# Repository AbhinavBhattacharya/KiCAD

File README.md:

# KiCAD
A repository of all my KiCAD projects

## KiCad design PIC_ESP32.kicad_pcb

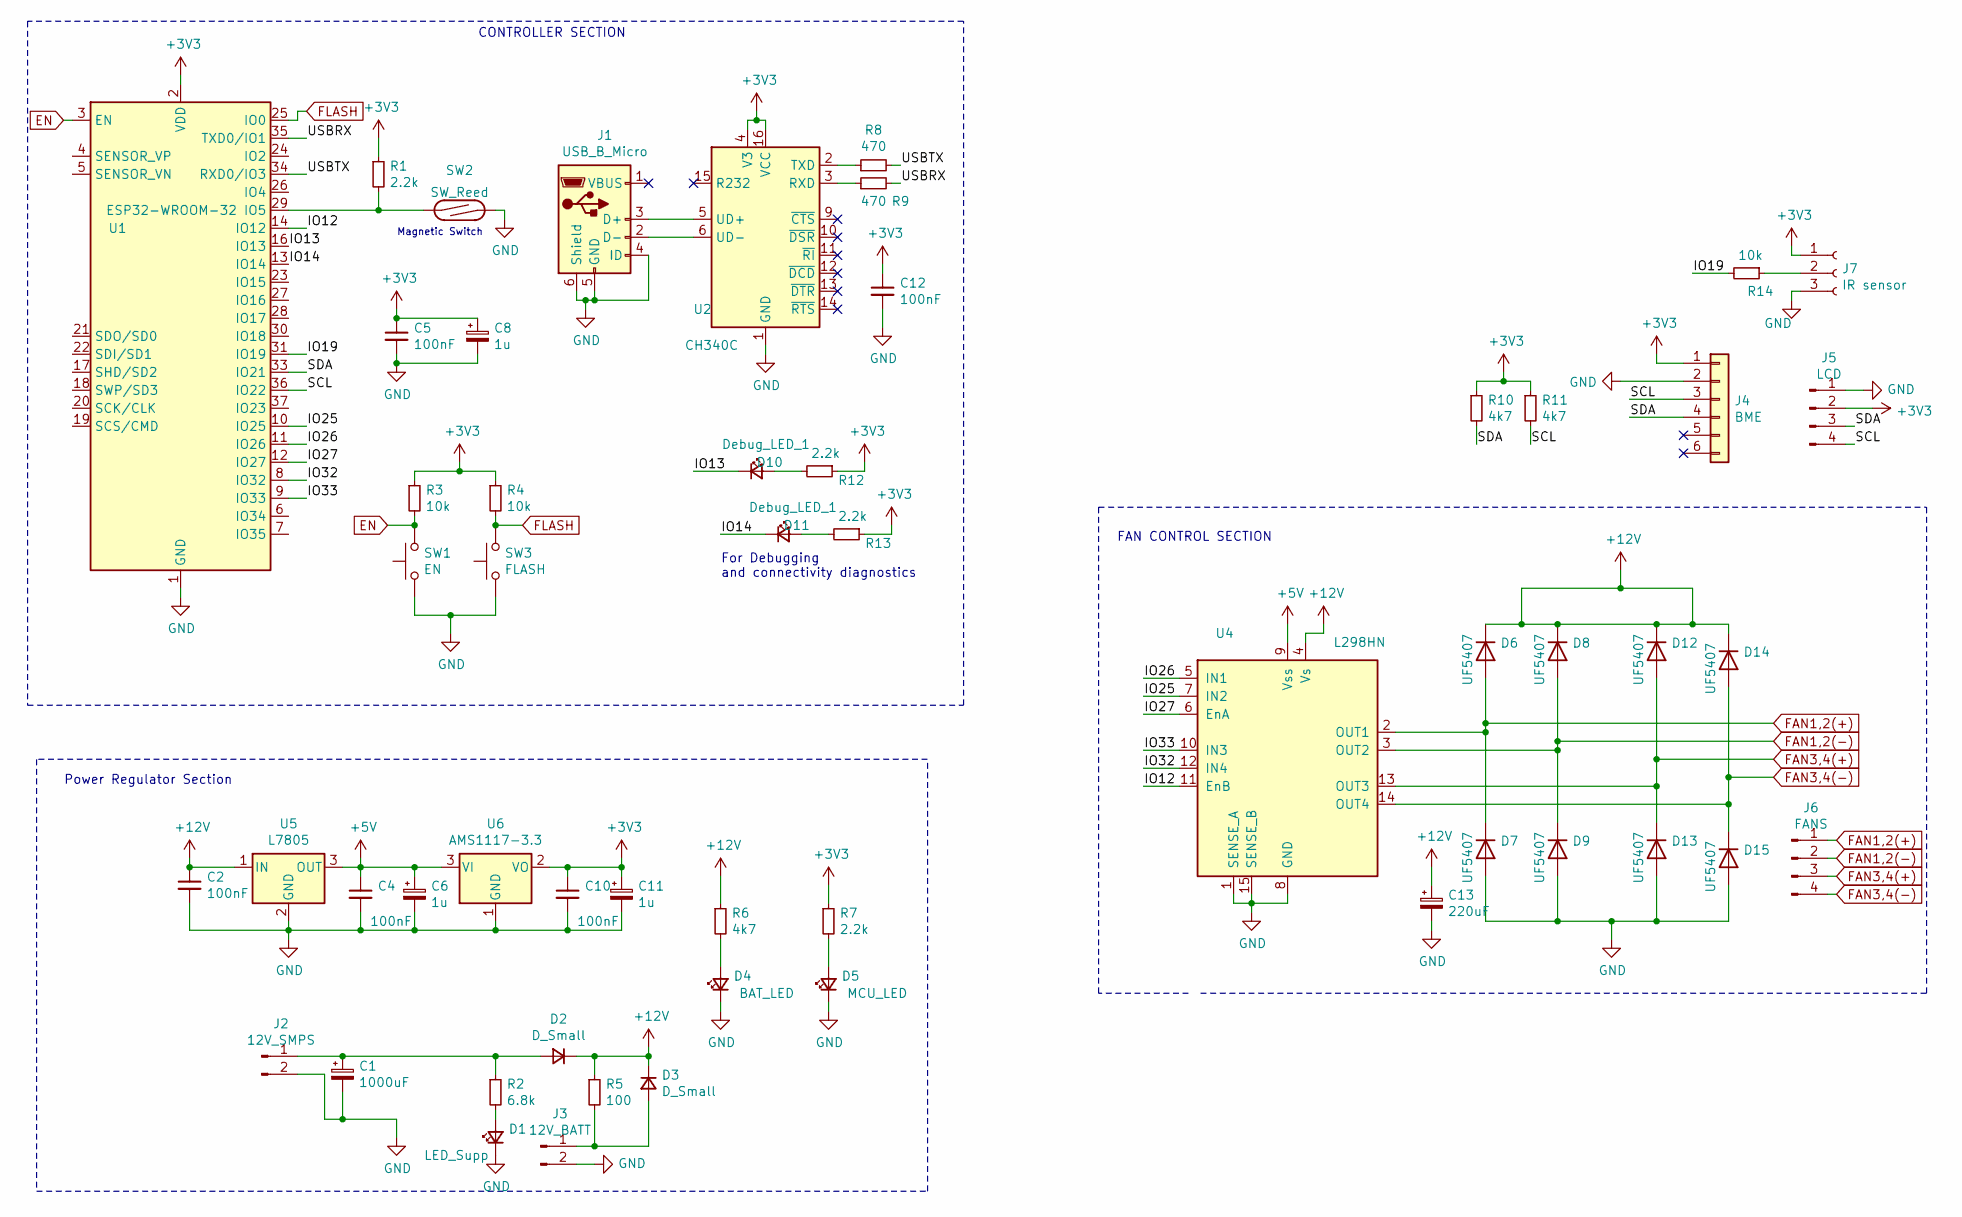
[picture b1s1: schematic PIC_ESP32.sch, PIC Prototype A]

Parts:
C1: 1000uF; CP_Radial_D10.0mm_P5.00mm
C2, C4, C5, C10, C12: 100nF; C_Disc_D3.8mm_W2.6mm_P2.50mm
C6, C8: 1u; CP_Radial_D5.0mm_P2.00mm
C11: 1u; CP_Radial_D5.0mm_P2.50mm
C13: 220uF; CP_Radial_D12.5mm_P7.50mm
D1: LED_Supp; LED_1206_3216Metric_Pad1.42x1.75mm_HandSolder
D2, D3: D_Small; D_DO-15_P10.16mm_Horizontal
D4: BAT_LED; LED_1206_3216Metric_Pad1.42x1.75mm_HandSolder
D5: MCU_LED; LED_1206_3216Metric_Pad1.42x1.75mm_HandSolder
D6, D7, D8, D9, D12, D13, D14, D15: UF5407; D_DO-201AD_P15.24mm_Horizontal
D10, D11: Debug_LED_1; LED_1206_3216Metric_Pad1.42x1.75mm_HandSolder
J1: USB_B_Micro; USB_Micro-B_Molex-105017-0001
J2: 12V_SMPS; AMASS_XT60-F_1x02_P7.20mm_Vertical
J3: 12V_BATT; AMASS_XT60-F_1x02_P7.20mm_Vertical
J4: BME; Molex_KK-254_AE-6410-06A_1x06_P2.54mm_Vertical
J5: LCD; Molex_KK-254_AE-6410-04A_1x04_P2.54mm_Vertical
J6: FANS; TerminalBlock_Phoenix_MKDS-1,5-4-5.08_1x04_P5.08mm_Horizont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
J7: IR sensor; PinHeader_1x03_P2.54mm_Vertical
R1: 2.2k; R_Axial_DIN0207_L6.3mm_D2.5mm_P10.16mm_Horizontal
R2: 6.8k; R_Axial_DIN0207_L6.3mm_D2.5mm_P10.16mm_Horizontal
R3, R4, R14: 10k; R_0805_2012Metric_Pad1.15x1.40mm_HandSolder
R5: 100; R_Axial_Power_L38.0mm_W6.4mm_P40.64mm
R6, R10, R11: 4k7; R_0805_2012Metric_Pad1.15x1.40mm_HandSolder
R7, R12, R13: 2.2k; R_0805_2012Metric_Pad1.15x1.40mm_HandSolder
R8, R9: 470; R_0805_2012Metric_Pad1.15x1.40mm_HandSolder
SW1: EN; SW_SPST_PTS645
SW2: SW_Reed; R_Box_L14.0mm_W5.0mm_P9.00mm
SW3: FLASH; SW_SPST_PTS645
U1: ESP32-WROOM-32
U2: CH340C; SOIC-16_3.9x9.9mm_P1.27mm
U4: L298HN; TO-220-15_P2.54x2.54mm_StaggerOdd_Lead4.58mm_Vertical
U5: L7805; TO-220-3_Vertical
U6: AMS1117-3.3; SOT-223-3_TabPin2

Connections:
+3V3: C5.1, C8.1, C10.1, C11.1, C12.1, J4.1, J5.2, J7.1, R1.1, R3.1, R4.1, R7.1, R10.1, R11.1, R12.1, R13.1, U1.2 (VDD), U2.4 (V3), U2.16 (VCC), U6.2 (VO)
+5V: C4.1, C6.1, U4.9 (Vss), U5.3 (OUT), U6.3 (VI)
+12V: C2.1, C13.1, D2.1 (K), D3.1 (K), D6.1 (K), D8.1 (K), D12.1 (K), D14.1 (K), R5.1, R6.1, U4.4 (Vs), U5.1 (IN)
/IO12: U1.14 (IO12), U4.11 (EnB)
/IO13: D10.1 (K), U1.16 (IO13)
/IO14: D11.1 (K), U1.13 (IO14)
/IO19: R14.2, U1.31 (IO19)
/IO25: U1.10 (IO25), U4.7 (IN2)
/IO26: U1.11 (IO26), U4.5 (IN1)
/IO27: U1.12 (IO27), U4.6 (EnA)
/IO32: U1.8 (IO32), U4.12 (IN4)
/IO33: U1.9 (IO33), U4.10 (IN3)
/SCL: J4.3, J5.4, R11.2, U1.36 (IO22)
/SDA: J4.4, J5.3, R10.2, U1.33 (IO21)
/USBRX: R9.2, U1.35 (TXD0/IO1)
/USBTX: R8.2, U1.34 (RXD0/IO3)
EN: R3.2, SW1.2, U1.3 (EN)
FAN1,2(+): D6.2 (A), D7.1 (K), J6.1, U4.2 (OUT1)
FAN1,2(-): D8.2 (A), D9.1 (K), J6.2, U4.3 (OUT2)
FAN3,4(+): D12.2 (A), D13.1 (K), J6.3, U4.13 (OUT3)
FAN3,4(-): D14.2 (A), D15.1 (K), J6.4, U4.14 (OUT4)
FLASH: R4.2, SW3.2, U1.25 (IO0)
GND: C1.2, C2.2, C4.2, C5.2, C6.2, C8.2, C10.2, C11.2, C12.2, C13.2, D1.1 (K), D4.1 (K), D5.1 (K), D7.2 (A), D9.2 (A), D13.2 (A), D15.2 (A), J1.4 (ID), J1.5 (GND), J1.6 (Shield), J2.2, J3.2, J4.2, J5.1, J7.3, SW1.1, SW2.2, SW3.1, U1.1 (GND), U1.15 (GND), U1.38 (GND), U1.39 (GND), U2.1 (GND), U4.1 (SENSE_A), U4.8 (GND), U4.15 (SENSE_B), U5.2 (GND), U6.1 (GND)
unnamed: C1.1, D2.2 (A), J2.1, R2.1
unnamed: D1.2 (A), R2.2
unnamed: D3.2 (A), J3.1, R5.2
unnamed: D4.2 (A), R6.2
unnamed: D5.2 (A), R7.2
unnamed: D10.2 (A), R12.2
unnamed: D11.2 (A), R13.2
unnamed: J1.2 (D-), U2.6 (UD-)
unnamed: J1.3 (D+), U2.5 (UD+)
unnamed: J7.2, R14.1
unnamed: R1.2, SW2.1, U1.29 (IO5)
unnamed: R8.1, U2.2 (TXD)
unnamed: R9.1, U2.3 (RXD)

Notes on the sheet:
Power Regulator Section
FAN CONTROL SECTION
CONTROLLER SECTION
For Debugging and connectivity diagnostics
Magnetic Switch

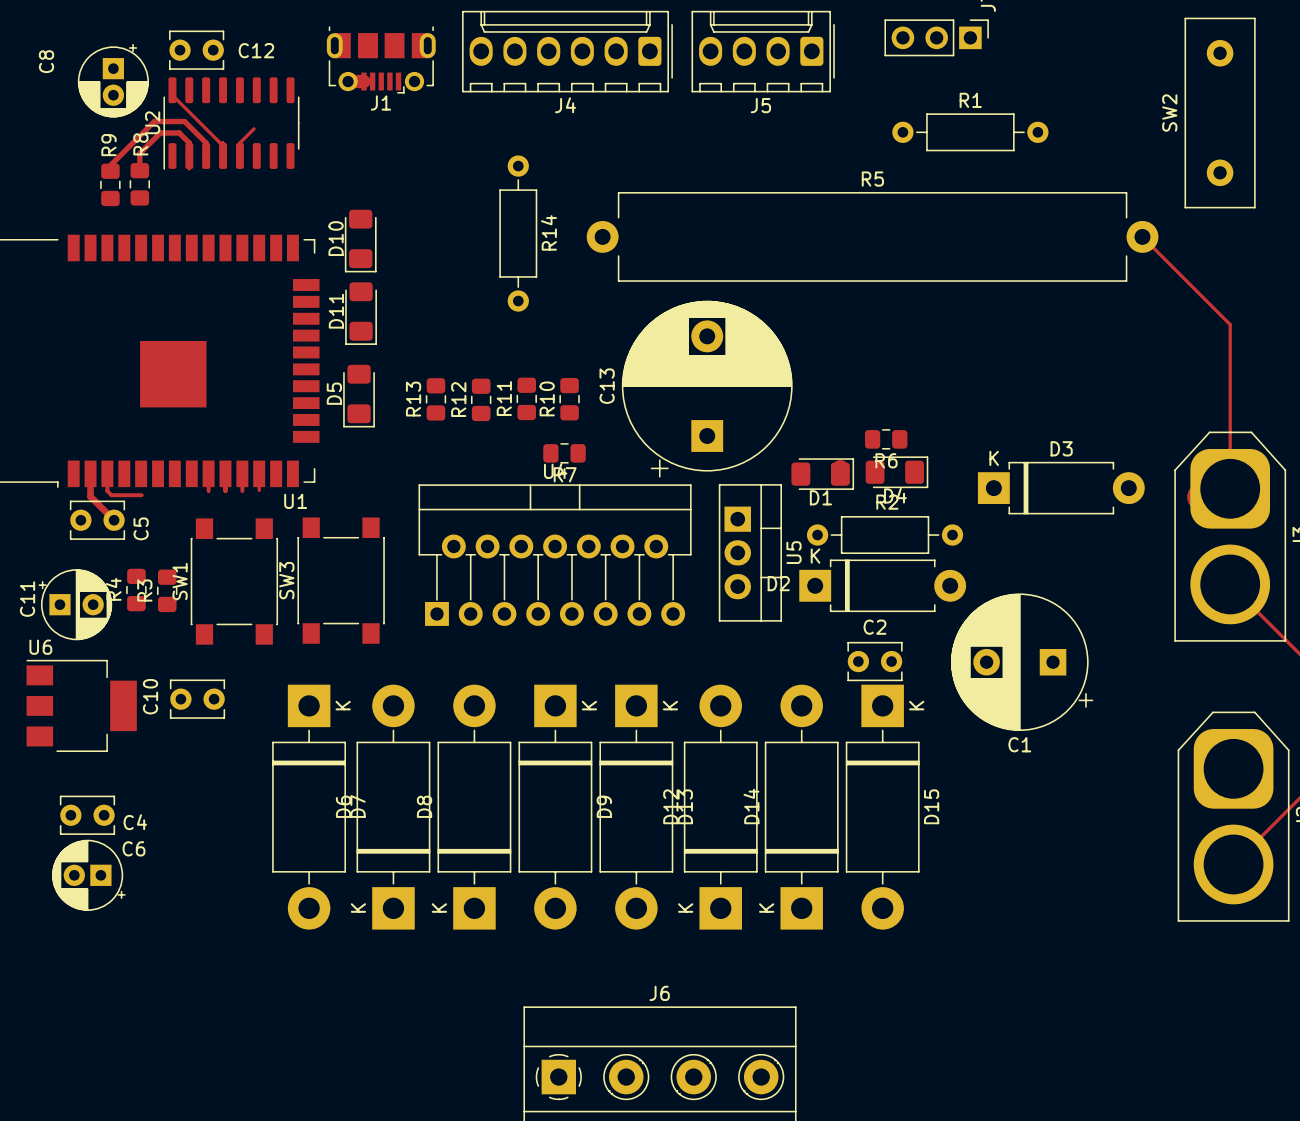
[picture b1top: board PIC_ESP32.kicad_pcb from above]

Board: 2 copper layers, 54 parts (0 on the bottom side), 36 nets.

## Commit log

2021-04-30 change 1
2021-04-30 added fuse
